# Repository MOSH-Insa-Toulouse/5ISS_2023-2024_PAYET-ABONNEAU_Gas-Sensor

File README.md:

# Sensor Gas Project by Alexis PAYET & Benjamin ABONNEAU

## Introduction

These days, the Internet of Things is becoming more and more prevalent, which is why it's interesting to look at how an object (a sensor, for example) is implemented from its creation to its deployment.

This is what the UF Smart Devices enabled us to do this year with a gas sensor. Starting with its manufacture during an internship at AIME, then tackling its schematic design and ending with its use and analysis.

In what follows, we'll look at the various stages we covered throughout the process.

## I. Manufacture of the gas sensor

During a week-long internship at AIME, we designed a gas sensor. Using various chemical processes, we were able to design nano-particles that we deposited on our sensor with the aim of making it intelligent. In order to design these nano-particles we followed a protocol that indicated a series of steps to be carried out, for example mixing different chemical substances together or simply cooking them at very high temperatures for a few minutes.

## II. Initial wiring

A few weeks later, having completed the design of our gas sensor, we were able to embark on the second stage of the project. The first stage involved wiring up the various components supplied. The aim was then to connect a gas sensor, retrieve its value using a program, send this value over a LoRaWAN network and finally retrieve it from an online application that would analyse it.

We used :
- An MQ-2 Grove gas sensor from Seeed
- An Arduino board to link all the components together and retrieve the sensor data via a mini program
- A board fitted with an RN2483A microchip for sending data over the LoRa network

Before starting the wiring, we had to do some soldering on the LoRa board. The board wasn't yet attached to the microchip, so it had to be soldered. We only soldered the pins we were interested in, namely : TX, RX, RST, 3V3 and GND. This allows us to power our chip and also send and receive data.

For the wiring, we chose to connect the gas sensor to pin A0 on the Arduino board and TX and RX on the LoRa board are connected to pin 10 and 11 respectively on the Arduino board. To power everything, we supply the Arduino board via the computer's USB port.

<div align="center">
<br />
<p>Photo of the wiring</p>
</div>

## III. Arduino program

Now that we had our wiring done, we had to ensure that we could retrieve the sensor data using a program.

To do this, we used two different Arduino programs. The first, DeviceInfo, enabled us to retrieve the information from our LoRa board so that we could register it on the LoRaWAN gateway and create our LoRa application.

<div align="center">
<br />
<p>DeviceInfo program</p>
</div>

Example of information retrieved with the program :
```
Device Information

EUI: 0004A30B00F49C7E
Battery: 3480
AppEUI: 0000000000000000
DevEUI: 0004A30B00F49C7E
Data Rate: 0
RX Delay 1: 1000
RX Delay 2: 2000

Use the EUI to register the device for OTAA
-------------------------------------------
```

The second Send program sends the data from the gas sensor to our LoRa network.

We had to configure a few lines to make the code work: the appEui and appKey fields, the TX and RX pins (corresponding to pins 10 and 11 as we saw earlier), and the GAZ_SENSOR_PIN pin corresponding to A0 and used to read the data output by the gas sensor. Once the configuration was complete, all that remained was to send the data using the sendBytes() function, which takes as its arguments a message to be sent (in our case the value of the gas sensor) and the size of the message (set to 2 because it is a two-digit value).

<div align="center">
<br />
<br />
<p>Send program</p>
</div>

## IV. NodeRED

Once the wiring had been done and our data sent to the LoRa network, we had to retrieve the message. To do this we used NodeRED, which is a very easy-to-use tool that makes it fairly simple to create applications. It comes in the form of blocks that can be attached to each other, allowing you to build your application as you go along. Each block corresponds to a function. Here we've used an MQTT block to listen for new incoming messages. Each time a message arrives (i.e. a new value from the gas sensor), we perform the various functions defined in NodeRED. In our case, we simply decode the message to make it clear so that we can display it in our application.

<div align="center">
<br />
<p>Representation of the NodeRED program</p>
</div>

## V. Drawing the schematic

Now that we know that our LoRa network works, we wanted to take it a step further by making our own board to use on our own gas sensor. First we had to create the schematic. This was done by making different blocks. We found the elements we had seen previously, such as the Arduino, the LoRa board and the gas sensor, but also new components such as the amplifier and the potentiometer, which will enable us to amplify the signal because the signal supplied by the Arduino's ADC is too weak. There's also a switch that lets you choose the gas sensor you want from the two available.

<div align="center">
<br />
<p>Global representation of the schematic</p>
</div><br />

<div align="center">
<br />
<p>Gas sensor diagram</p>
</div><br />

<div align="center">
<br />
<p>Switch diagram</p>
</div><br />

<div align="center">
<br />
<p>Amplifier diagram</p>
</div><br />

<div align="center">
<br />
<p>Potentiometer diagram</p>
</div><br />

<div align="center">
<br />
<p>LoRa board diagram</p>
</div>

## VI. Designing the PCB

Once the wiring diagram was finished, all that remained was to place the components on the board and connect them together. The most difficult step was to think about how to arrange the components on the PCB, as the wires can't cross each other.

<div align="center">
<br />
<p>PCB representation in the editor</p>
</div><br />

<div align="center">
<br />
<br />
<p>PCB representation in 3D view</p>
</div>

## Future Work

Unfortunately we haven't had time to print our PCB, so the first thing to do would be to print it out and then carry out a few tests to make sure it works. Also, our NodeRED application isn't super-developed and a graphical interface to be able to detect a gas change might be interesting to implement.

## Conclusion

This project has enabled us to develop our technical skills in different areas while learning new ones. For example, the KiCad software is one of the things we'd never used before and it was interesting to discover how you can make fairly simplistic maps once you've mastered it.

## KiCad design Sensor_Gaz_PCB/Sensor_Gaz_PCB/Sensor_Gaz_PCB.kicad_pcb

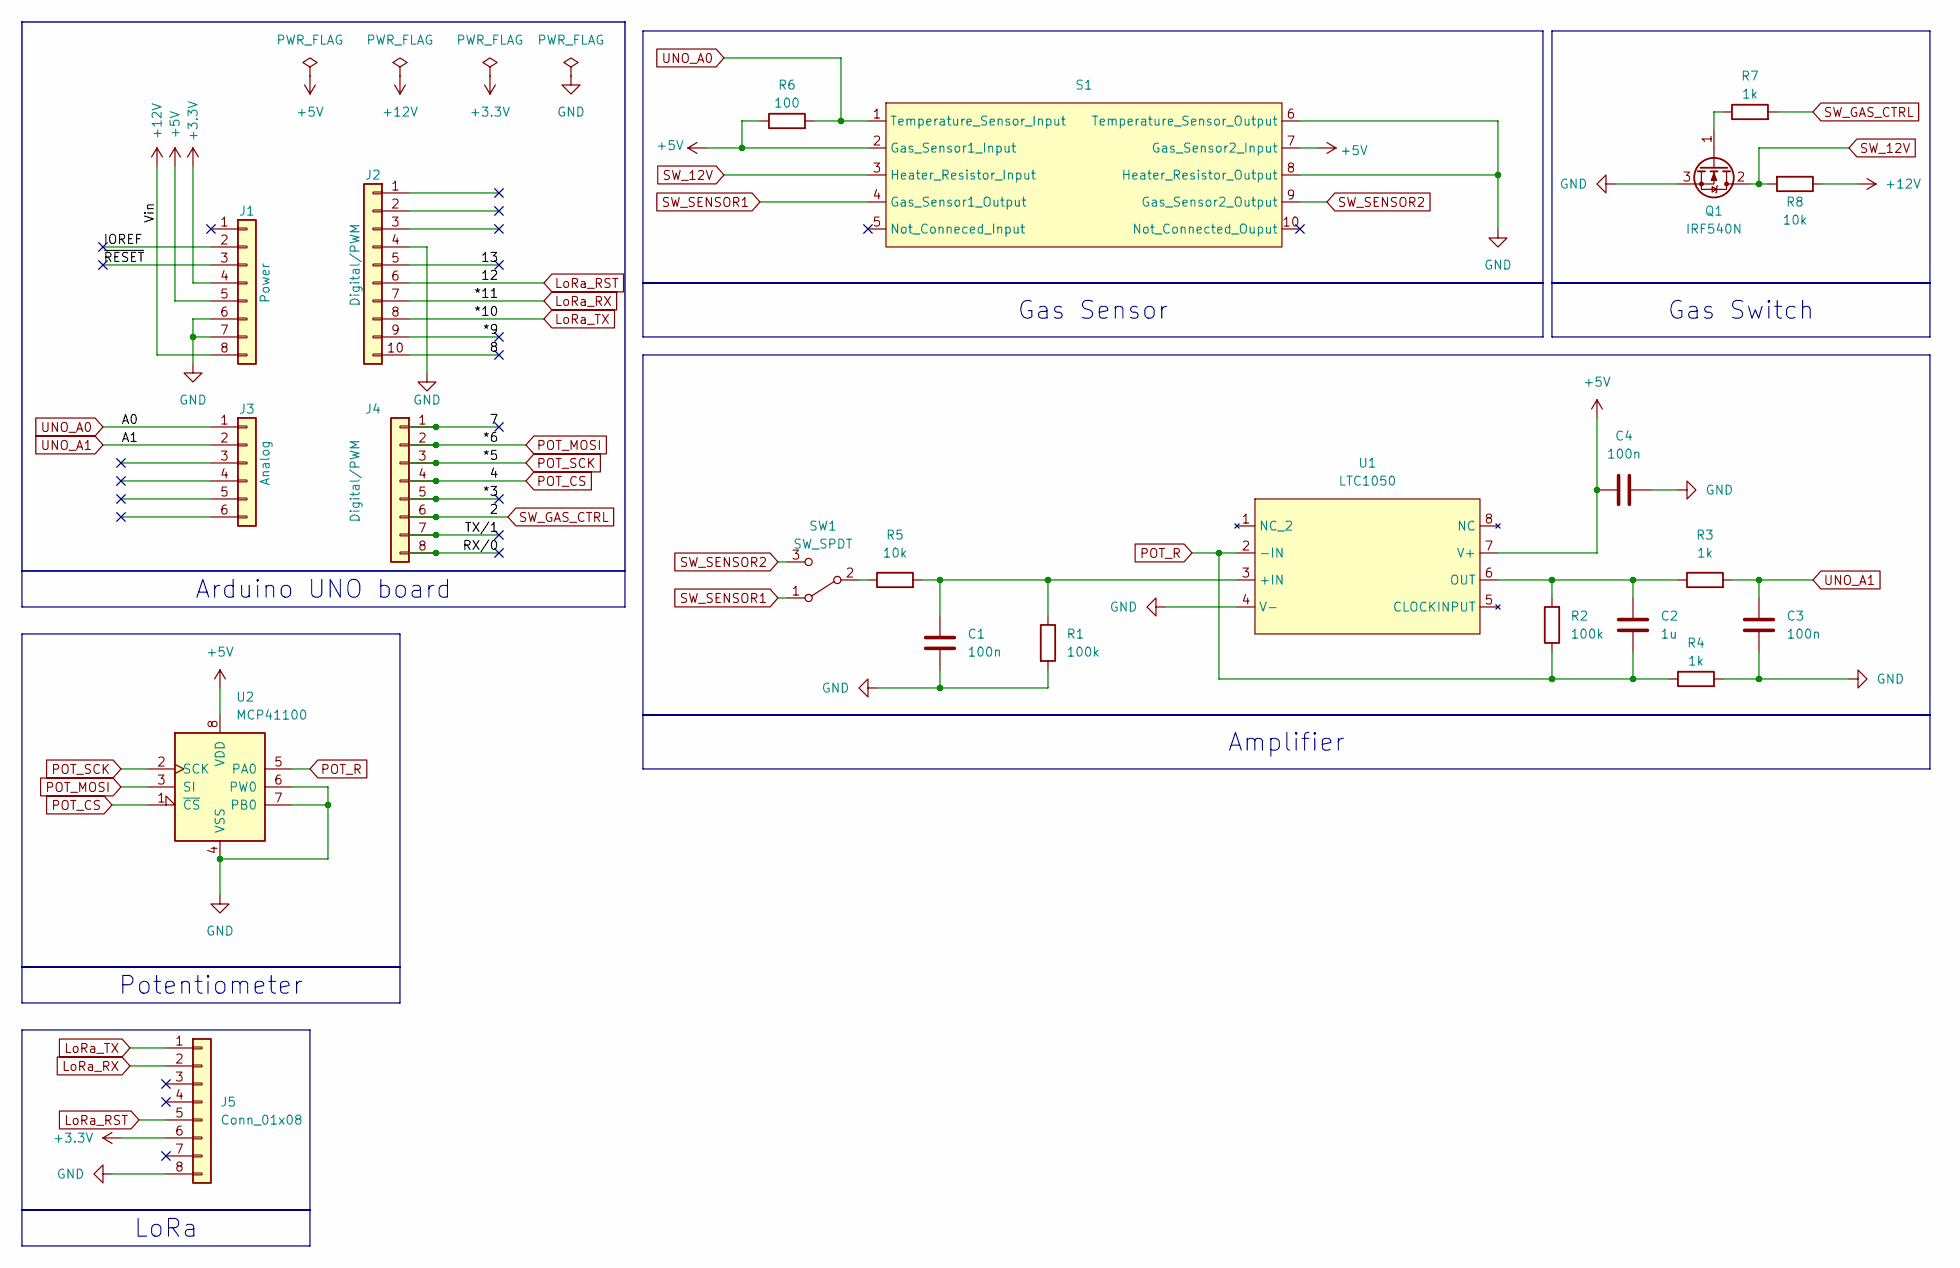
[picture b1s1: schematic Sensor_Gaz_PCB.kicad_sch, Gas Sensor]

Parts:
C1, C3, C4: 100n; C_Rect_L9.0mm_W5.1mm_P7.50mm_MKT
C2: 1u; C_Rect_L9.0mm_W5.1mm_P7.50mm_MKT
J1: Power; PinSocket_1x08_P2.54mm_Vertical
J2: Digital/PWM; PinSocket_1x10_P2.54mm_Vertical
J3: Analog; PinSocket_1x06_P2.54mm_Vertical
J4: Digital/PWM; PinSocket_1x08_P2.54mm_Vertical
J5: Conn_01x08; PinSocket_1x08_P2.54mm_Vertical
Q1: IRF540N; TO-220-3_Vertical
R1, R2: 100k; R_Axial_DIN0204_L3.6mm_D1.6mm_P5.08mm_Horizontal
R3, R4, R7: 1k; R_Axial_DIN0204_L3.6mm_D1.6mm_P5.08mm_Horizontal
R5, R8: 10k; R_Axial_DIN0204_L3.6mm_D1.6mm_P5.08mm_Horizontal
R6: 100; R_Axial_DIN0204_L3.6mm_D1.6mm_P5.08mm_Horizontal
S1: Sensor_Gas
SW1: SW_SPDT; SW_Push_2P2T_Toggle_CK_PVA2xxH2xxxxxxV2
U1: LTC1050
U2: MCP41100; DIP-8_W7.62mm

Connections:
+3.3V: J1.4, J5.6
+5V: C4.1, J1.5, R6.1, S1.2 (Gas_Sensor1_Input), S1.7 (Gas_Sensor2_Input), U1.7 (V+), U2.8 (VDD)
+12V: J1.8, R8.1
/7: J4.1
/8: J2.10
/13: J2.5
/*3: J4.5
/*9: J2.9
/IOREF: J1.2
/RX/0: J4.8
/TX/1: J4.7
/~RESET: J1.3
GND: C1.2, C3.2, C4.2, J1.6, J1.7, J2.4, J5.8, Q1.3 (S), R1.2, R4.2, S1.6 (Temperature_Sensor_Output), S1.8 (Heater_Resistor_Output), U1.4 (V-), U2.4 (VSS), U2.6 (PW0), U2.7 (PB0)
LoRa_RST: J2.6, J5.5
LoRa_RX: J2.7, J5.2
LoRa_TX: J2.8, J5.1
unnamed: Q1.1 (G), R7.1
unnamed: R5.1, SW1.2 (B)
unnamed: C1.1, R1.1, R5.2, U1.3 (+IN)
unnamed: C2.1, R2.2, R3.1, U1.6 (OUT)
POT_CS: J4.4, U2.1 (~CS)
POT_MOSI: J4.2, U2.3 (SI)
POT_R: C2.2, R2.1, R4.1, U1.2 (-IN), U2.5 (PA0)
POT_SCK: J4.3, U2.2 (SCK)
SW_12V: Q1.2 (D), R8.2, S1.3 (Heater_Resistor_Input)
SW_GAS_CTRL: J4.6, R7.2
SW_SENSOR1: S1.4 (Gas_Sensor1_Output), SW1.1 (A)
SW_SENSOR2: S1.9 (Gas_Sensor2_Output), SW1.3 (C)
UNO_A0: J3.1, R6.2, S1.1 (Temperature_Sensor_Input)
UNO_A1: C3.1, J3.2, R3.2

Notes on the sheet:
LoRa
Potentiometer
Amplifier
Arduino UNO board
Gas Sensor
Gas Switch

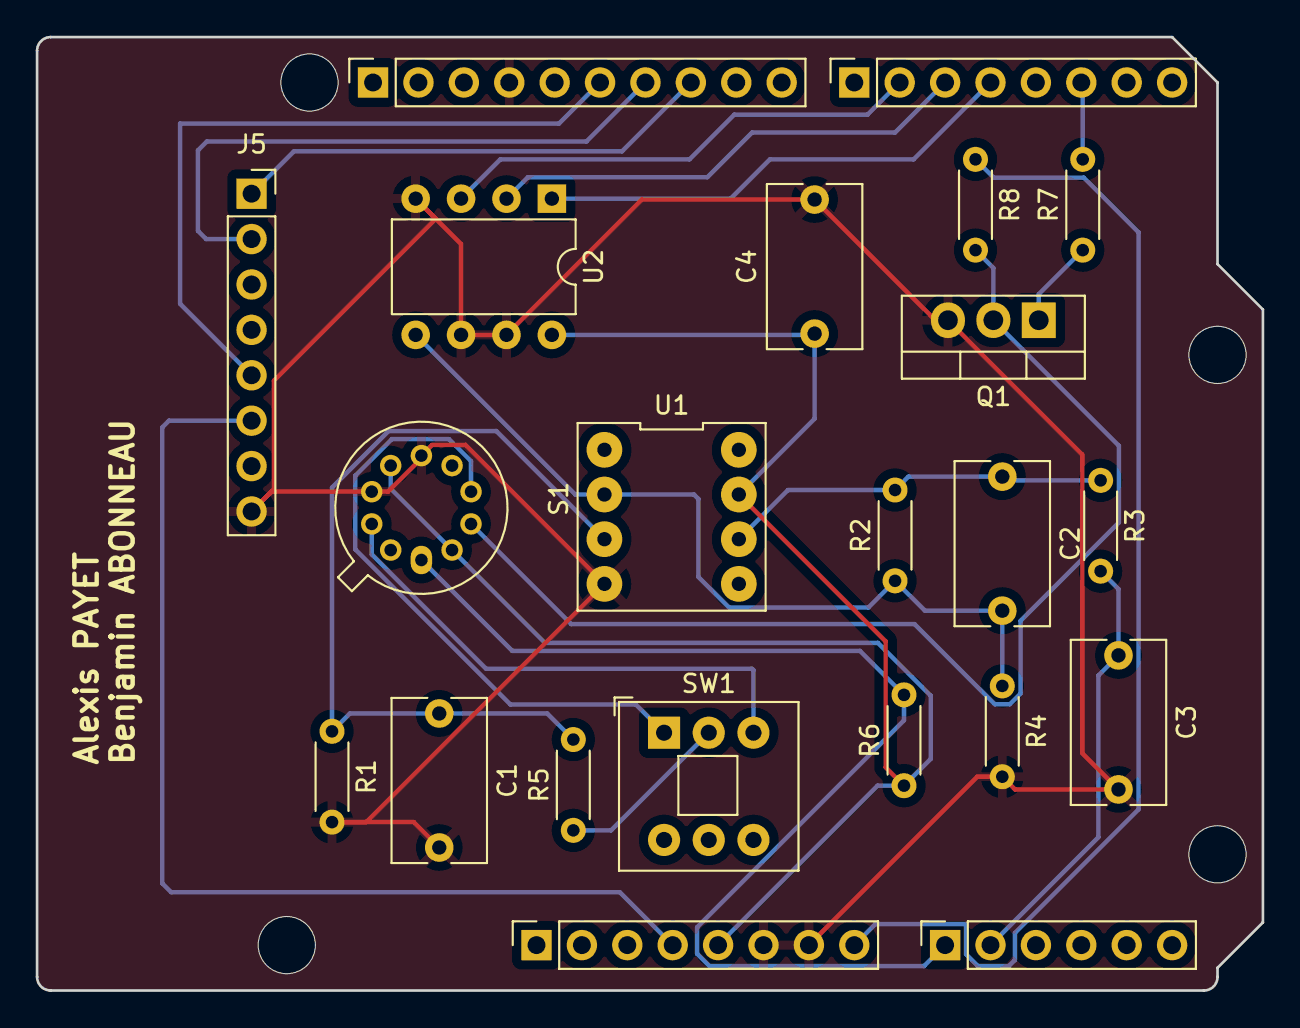
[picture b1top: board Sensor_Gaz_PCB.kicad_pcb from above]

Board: 2 copper layers, 68.6 x 53.3 mm, 26 parts (0 on the bottom side), 21 nets.

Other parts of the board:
MH1, MH2, MH3, MH4: MountingHole_3.2mm

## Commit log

2024-02-29 Initial commit.
